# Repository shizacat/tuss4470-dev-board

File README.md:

# TUSS4470 Homemade Evaluation Board

This project aims to design and build a PCB evaluation board for the **TUSS4470** ultrasonic driver that can be manufactured in a home workshop environment.

The main objective is to create a simple, low-cost board that allows testing and characterization of the TUSS4470 in real operating conditions without relying on expensive commercial development kits.

The board will:
- Provide proper power supply and decoupling for the TUSS4470
- Allow connection of an external ultrasonic transducer
- Include basic protection and filtering components
- Be optimized for manual PCB fabrication and soldering (through-hole where possible, reasonable trace widths, minimal layer complexity). Two layer board will be needed.

Requirements:
- Created in KiCad 9.x

## CI/CD — Jobs for home fabrication

On release or manual run, the **KiCad PCB Jobs** workflow produces the **main** artifact (folder `main/` in `kicad-job-main.zip`). It is set up for **home PCB fabrication using the film photoresist method**:

| Layer | Processing | Purpose |
|-------|------------|--------|
| **F (front)** | Inverted and mirrored (mirror + negative) | Print on transparent film for top-side photoresist exposure |
| **B (back)** | Inverted only (negative) | Print on film for bottom-side exposure |

The **main** job outputs layer PDFs (F.Cu, B.Cu), drill files (Excellon), and BOM (CSV). Use them to print masks on transparent film and then UV-expose the photoresist-coated blank.

## License

This project is licensed under the MIT License — see the [LICENSE](LICENSE) file for details.

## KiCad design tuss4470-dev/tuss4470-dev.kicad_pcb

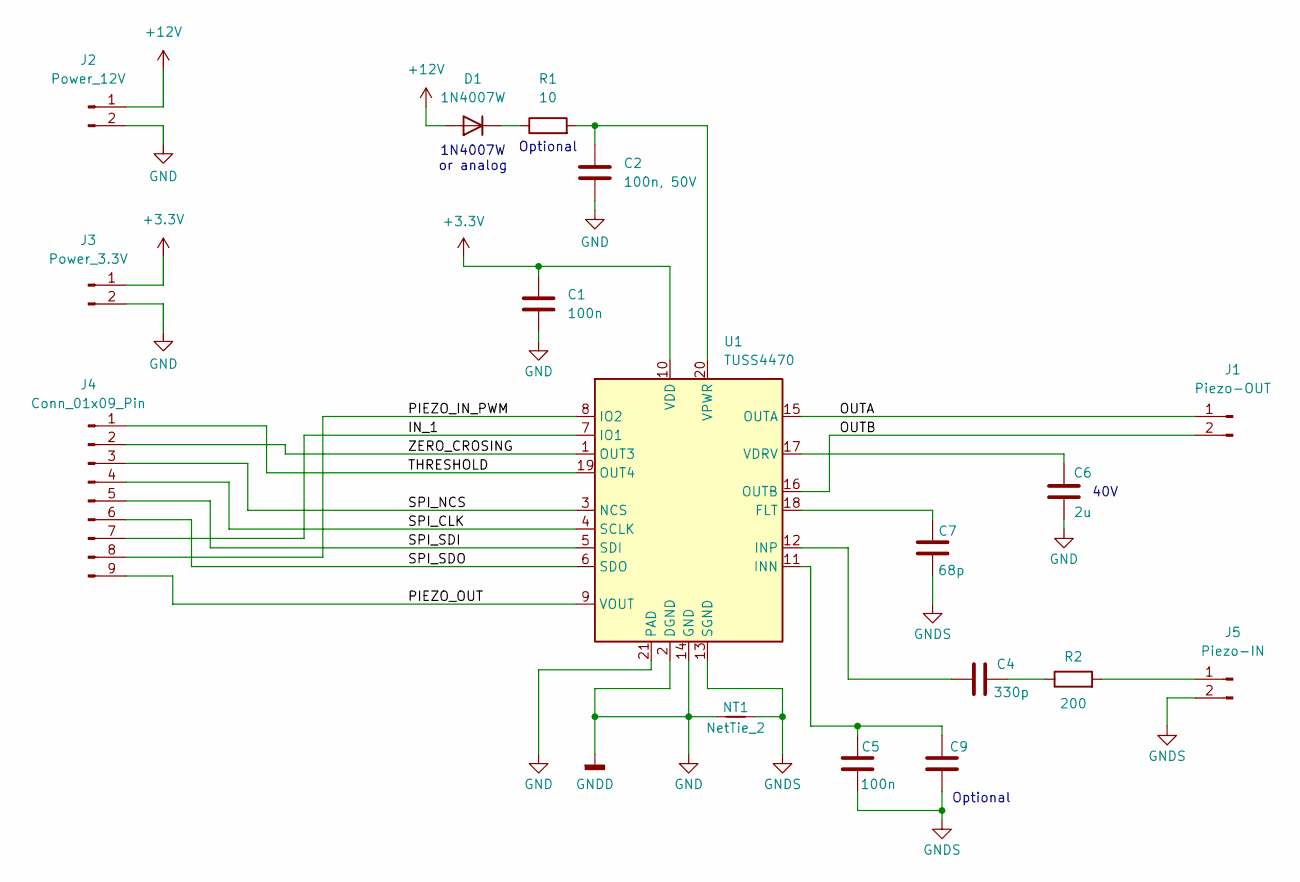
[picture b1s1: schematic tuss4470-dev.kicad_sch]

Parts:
C1, C5: 100n; C_0603_1608Metric
C2: 100n, 50V; C_0603_1608Metric
C4: 330p; C_0603_1608Metric
C6: 2u; C_0805_2012Metric
C7: 68p; C_0603_1608Metric
C9: C_0603_1608Metric
D1: 1N4007W; D_SOD-123
J1: Piezo-OUT; PinHeader_1x02_P2.54mm_Vertical
J2: Power_12V; PinHeader_1x02_P2.54mm_Vertical
J3: Power_3.3V; PinHeader_1x02_P2.54mm_Vertical
J4: Conn_01x09_Pin; PinHeader_1x09_P2.54mm_Vertical
J5: Piezo-IN; PinHeader_1x02_P2.54mm_Vertical
NT1: NetTie_2; NetTie-2_SMD_Pad0.2mm
R1: 10; R_0603_1608Metric
R2: 200; R_0603_1608Metric
U1: TUSS4470; WQFN-20-1EP_4x4mm_P0.5mm_EP2.7x2.7mm

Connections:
+3.3V: C1.1, J3.1, U1.10 (VDD)
+12V: D1.2 (A), J2.1
/IN_1: J4.7, U1.7 (IO1)
/OUTA: J1.1, U1.15 (OUTA)
/OUTB: J1.2, U1.16 (OUTB)
/PIEZO_IN_PWM: J4.8, U1.8 (IO2)
/PIEZO_OUT: J4.9, U1.9 (VOUT)
/SPI_CLK: J4.4, U1.4 (SCLK)
/SPI_NCS: J4.3, U1.3 (NCS)
/SPI_SDI: J4.5, U1.5 (SDI)
/SPI_SDO: J4.6, U1.6 (SDO)
/THRESHOLD: J4.1, U1.19 (OUT4)
/ZERO_CROSING: J4.2, U1.1 (OUT3)
GND: C1.2, C2.2, C6.2, J2.2, J3.2, NT1.1, U1.2 (DGND), U1.14 (GND), U1.21 (PAD)
GNDS: C5.2, C7.1, C9.1, J5.2, NT1.2, U1.13 (SGND)
unnamed: C4.2, R2.1
unnamed: D1.1 (K), R1.1
unnamed: J5.1, R2.2
unnamed: C7.2, U1.18 (FLT)
unnamed: C5.1, C9.2, U1.11 (INN)
unnamed: C4.1, U1.12 (INP)
unnamed: C6.1, U1.17 (VDRV)
unnamed: C2.1, R1.2, U1.20 (VPWR)

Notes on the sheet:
Optional
40V
1N4007W or analog

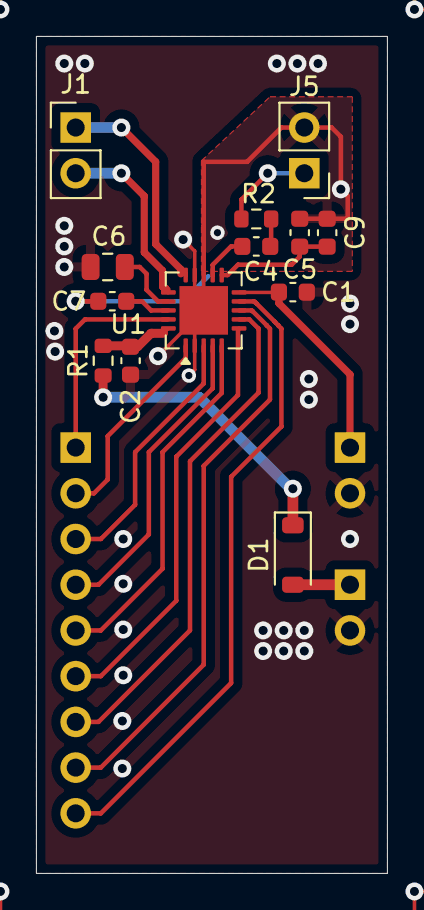
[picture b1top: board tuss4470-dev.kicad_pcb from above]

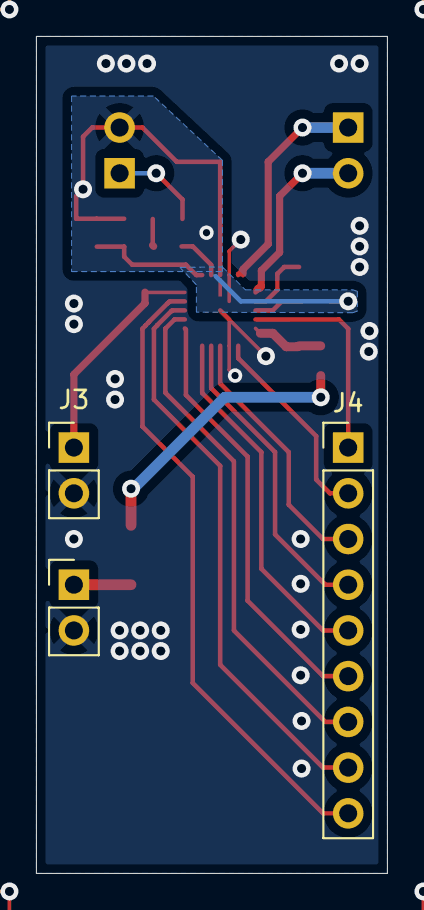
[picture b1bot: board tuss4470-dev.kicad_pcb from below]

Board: 2 copper layers, 19.5 x 46.5 mm, 17 parts (3 on the bottom side), 23 nets.

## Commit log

2026-02-25 Add readme
2026-02-25 Add ignore
2026-02-25 Add board
2026-02-25 rename readme
2026-02-25 Add action export to pdf sch
2026-02-25 Add pcb
2026-02-25 update ignore
2026-02-28 update docs
2026-02-28 Add export into release
2026-02-28 as zip
2026-02-28 Add export into release (#2)
    Export only release
2026-02-28 add jobs
2026-02-28 Add action
2026-02-28 update name
2026-02-28 add bom export
2026-02-28 Export jobs (#3)
    Add action for job
2026-02-28 add license
2026-02-28 Fix jobs
2026-02-28 update action
2026-02-28 Fix a
2026-02-28 add artifact
2026-02-28 remove art
2026-02-28 on release
2026-02-28 add action (#4)
    Add interaction bom action
2026-02-28 Add changelog
